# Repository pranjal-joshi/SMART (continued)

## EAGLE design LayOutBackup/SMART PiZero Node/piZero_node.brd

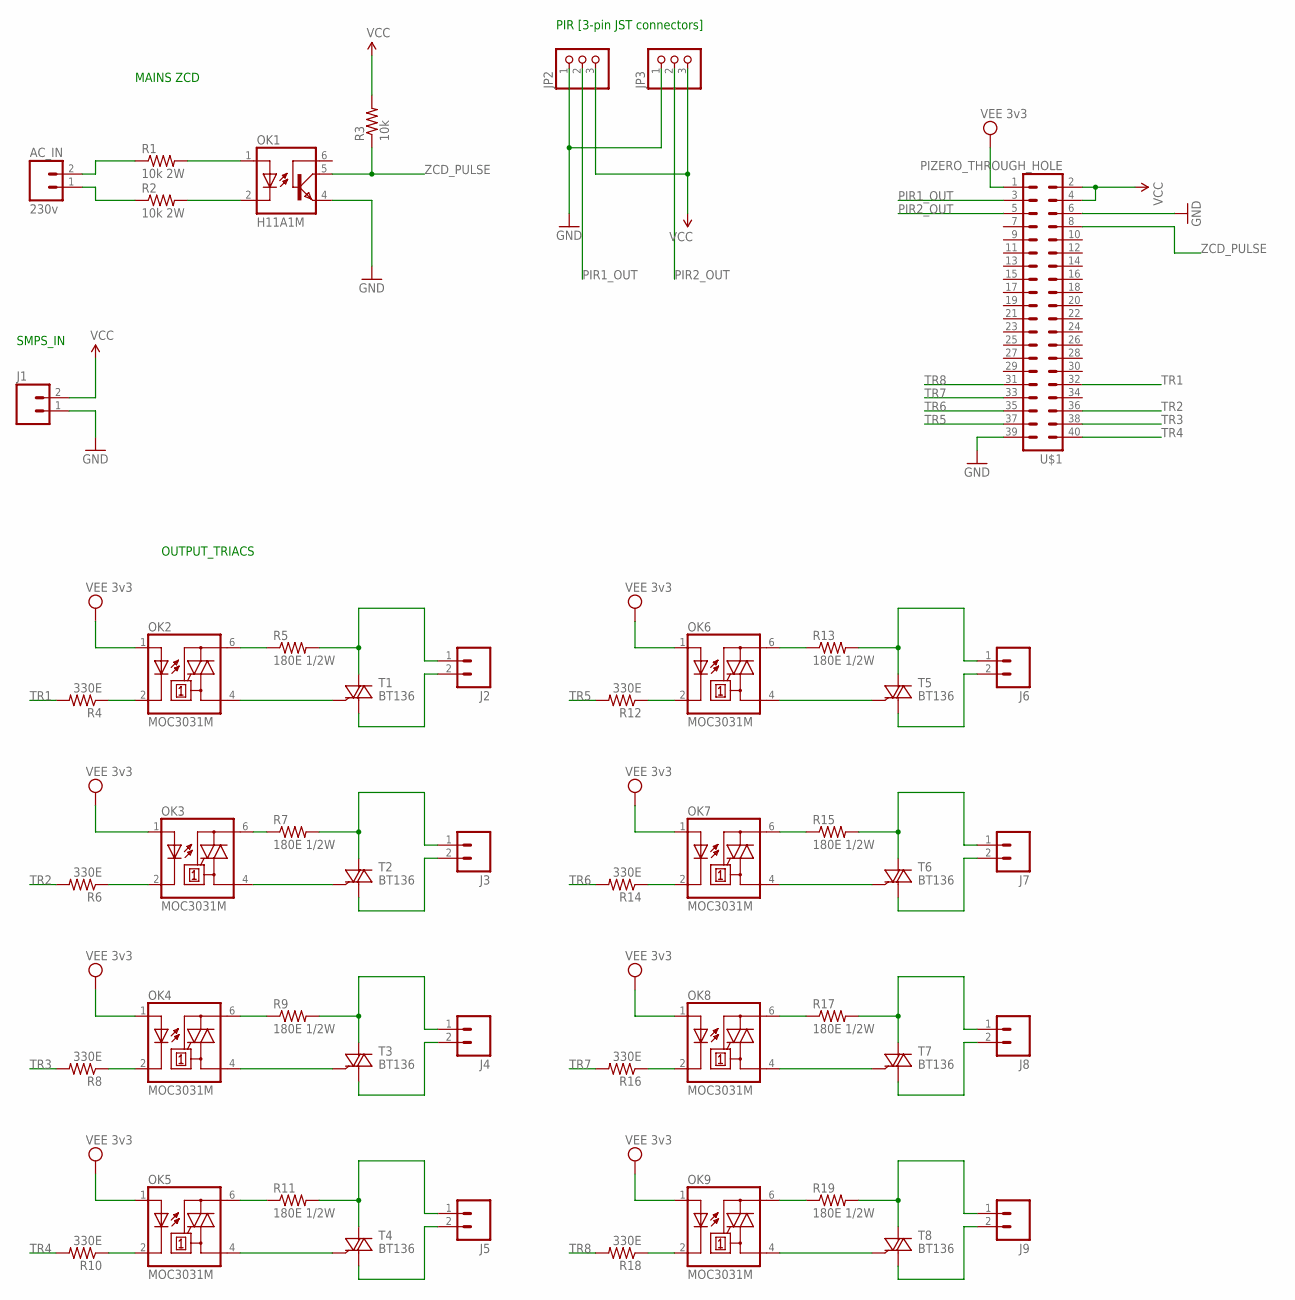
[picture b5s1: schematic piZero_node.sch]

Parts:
AC_IN: 230v; SCREWTERMINAL-3.5MM-2_LOCK
J1, J2, J3, J4, J5, J6, J7, J8, J9: M023.5MM_LOCK; SCREWTERMINAL-3.5MM-2_LOCK
JP2, JP3: PINHD-1X3; 1X03
OK1: H11A1M; DIL06
OK2, OK3, OK4, OK5, OK6, OK7, OK8, OK9: MOC3031M; DIL06
R1, R2: 10k 2W; AXIAL-0.8
R3: 10k; AXIAL-0.4
R4, R6, R8, R10, R12, R14, R16, R18: 330E; AXIAL-0.4
R5, R7, R9, R11, R13, R15, R17, R19: 180E 1/2W; AXIAL-0.5
T1, T2, T3, T4, T5, T6, T7, T8: BT136; TO220AB
U$1: PIZERO_THROUGH_HOLE; PIZERO_THOUGH_HOLE

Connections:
GND: J1.1, JP2.1, JP3.1, OK1.4 (EMI), U$1.6, U$1.39
unnamed: AC_IN.2, R1.P$1 (1)
unnamed: AC_IN.1, R2.P$1 (1)
unnamed: OK1.1 (A), R1.P$2 (2)
unnamed: OK1.2 (C), R2.P$2 (2)
unnamed: OK3.6 (A2), R7.P$1 (1)
unnamed: OK2.6 (A2), R5.P$1 (1)
unnamed: J2.1, R5.P$2 (2), T1.2 (A2)
unnamed: OK2.4 (A1), T1.3 (G)
unnamed: J2.2, T1.1 (A1)
unnamed: OK2.2 (C), R4.P$1 (1)
unnamed: J3.1, R7.P$2 (2), T2.2 (A2)
unnamed: OK3.4 (A1), T2.3 (G)
unnamed: J3.2, T2.1 (A1)
unnamed: OK3.2 (C), R6.P$1 (1)
unnamed: OK4.6 (A2), R9.P$1 (1)
unnamed: J4.1, R9.P$2 (2), T3.2 (A2)
unnamed: OK4.4 (A1), T3.3 (G)
unnamed: J4.2, T3.1 (A1)
unnamed: OK4.2 (C), R8.P$1 (1)
unnamed: OK5.6 (A2), R11.P$1 (1)
unnamed: J5.1, R11.P$2 (2), T4.2 (A2)
unnamed: OK5.4 (A1), T4.3 (G)
unnamed: J5.2, T4.1 (A1)
unnamed: OK5.2 (C), R10.P$1 (1)
unnamed: OK6.6 (A2), R13.P$1 (1)
unnamed: J6.1, R13.P$2 (2), T5.2 (A2)
unnamed: OK6.4 (A1), T5.3 (G)
unnamed: J6.2, T5.1 (A1)
unnamed: OK6.2 (C), R12.P$1 (1)
unnamed: OK7.6 (A2), R15.P$1 (1)
unnamed: J7.1, R15.P$2 (2), T6.2 (A2)
unnamed: OK7.4 (A1), T6.3 (G)
unnamed: J7.2, T6.1 (A1)
unnamed: OK7.2 (C), R14.P$1 (1)
unnamed: OK8.6 (A2), R17.P$1 (1)
unnamed: J8.1, R17.P$2 (2), T7.2 (A2)
unnamed: OK8.4 (A1), T7.3 (G)
unnamed: J8.2, T7.1 (A1)
unnamed: OK8.2 (C), R16.P$1 (1)
unnamed: OK9.6 (A2), R19.P$1 (1)
unnamed: J9.1, R19.P$2 (2), T8.2 (A2)
unnamed: OK9.4 (A1), T8.3 (G)
unnamed: J9.2, T8.1 (A1)
unnamed: OK9.2 (C), R18.P$1 (1)
PIR1_OUT: JP2.2, U$1.3
PIR2_OUT: JP3.2, U$1.5
TR1: R4.P$2 (2), U$1.32
TR2: R6.P$2 (2), U$1.36
TR3: R8.P$2 (2), U$1.38
TR4: R10.P$2 (2), U$1.40
TR5: R12.P$2 (2), U$1.37
TR6: R14.P$2 (2), U$1.35
TR7: R16.P$2 (2), U$1.33
TR8: R18.P$2 (2), U$1.31
VCC: J1.2, JP2.3, JP3.3, R3.P$2 (2), U$1.2, U$1.4
VEE: OK2.1 (A), OK3.1 (A), OK4.1 (A), OK5.1 (A), OK6.1 (A), OK7.1 (A), OK8.1 (A), OK9.1 (A), U$1.1
ZCD_PULSE: OK1.5 (COL), R3.P$1 (1), U$1.8

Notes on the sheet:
MAINS ZCD
SMPS_IN
PIR [3-pin JST connectors]
OUTPUT_TRIACS

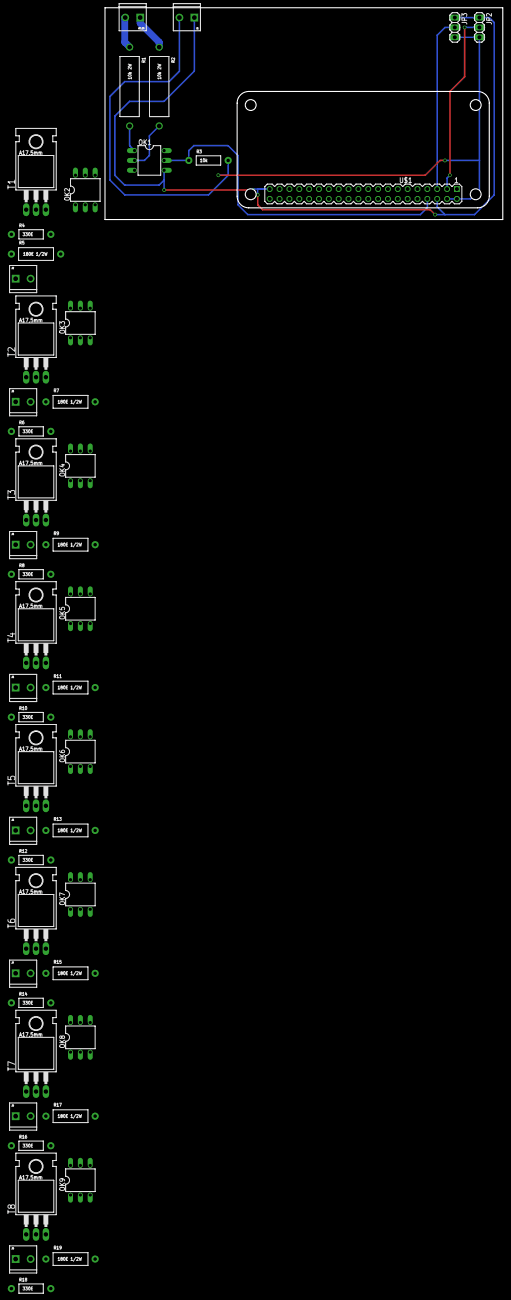
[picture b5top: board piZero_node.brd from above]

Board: 2 copper layers, 102.5 x 54.6 mm, 49 parts (0 on the bottom side), 58 nets.

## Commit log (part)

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2020-06-14 sub to gateway if net is available
2020-06-14 TODO: implement routing in decisionMaker
2020-06-14 broadcastStateChanged added
2020-06-14 getState bug fixed and optimized
2020-06-14 bugfixes
2020-06-14 Gateway routing impeoved TODO - dbg mesh.stop
2020-06-16 ntp added while mqtt connection
2020-06-16 NTP broadcast packet added
2020-06-16 ntpStruct added
2020-06-16 NTP functions added
2020-06-17 TODO - Impliment timer packet
2020-06-18 timeStruct added
2020-06-18 TODO - implement jsonTimerParser
2020-06-18 timerStructure updated
2020-06-18 save and load timer implemented
2020-06-18 parsers added to decisionMaker
2020-06-18 parseTimer and parseNTP implemented
2020-06-18 optimized
2020-06-18 debug mesh connection - instability
2020-06-19 minor improvements
2020-06-20 Major bugfix - Mesh disconnect on ntp.begin()
2020-06-20 scan MESH if TARGET unavailable to acquire channel
    Also stop searchTargetTask if anyone is ROOT because its online
2020-06-21 mesh ssid & pass added
2020-06-21 Mesh SSID, PASS & channel JS added
2020-06-21 todo - fix target ssid not found bug
2020-06-21 soft_reset added
2020-06-21 personalize MESH network while CONF
    JSON_BUF_SIZE > 768 will cause a PANIC dump in stateChangedBroadcast
2020-06-21 get set Raw methods added
2020-06-21 struct updated
2020-06-21 todo - Debug fsys.loadTimers dump
2020-06-21 timerSchedHandlerTask added
2020-06-21 Check & implement TODOs
2020-06-22 timerStruct now have ignore time of 60 sec
2020-06-22 loadTimers PANIC resolved, not using fsys.loadTimers now
2020-06-23 preprocessors added for SWITCHING & SENSOR
2020-06-23 constants replaced with #define
2020-06-23 SensorLink JSON parser added
2020-06-23 Sensor Functions added
2020-06-23 Check todos!
2020-06-24 get set by sensor methods added
2020-06-25 get set by Timer added
2020-06-25 New methods added and bugfixes
2020-06-25 Sensor broadcast parser implemented
2020-06-25 Light & DHT removed
2020-06-25 todo - implement mesh sensor to MQTT routing
2020-06-26 mesh json print on connection callback
2020-06-26 Fingerprints added
2020-06-30 topic added to sensor_broadcast
2020-06-30 sensor_broadcast publish routing added
2020-06-30 Flutter project created
2020-06-30 OTA save/load added
2020-06-30 OTA methods added
2020-06-30 OTA update handler implemented
2020-06-30 OTA packet panic core fixed
2020-07-03 SENSOR PIN - FUNCTION_3
2020-07-03 Pin switching between Serial & GPIO for ESP-01
2020-07-03 config updated for NOD=2, NOD=1
2020-07-03 IO class updated for NOD=2, NOD=1
2020-07-03 initiali update NOD=2, NOD=1 implemented
2020-07-03 WIll Message implemented
2020-07-03 Routing of STATUS packet from Gateway -> MQTT
2020-07-03 Vector_Link added for reflecting STATUS from Mesh -> MQTT
    Review To-Dos
2020-07-05 ID implemented for AsyncOTA
2020-07-05 Vector Link implemented to send STATTUS to MQTT
2020-07-05 JSON fixes
2020-07-05 stateVar inverted for ACTIVE LOW in NoD < 4
2020-07-05 Sensor improvements
2020-07-05 ToDo: Sensor GPIO selection & testing
2020-07-06 PIN config changed for Sensor
2020-07-06 Replaced ElegantOTA with ESP8266HTTPUpdater
    #define WEBSERVER_H removes redeclaration error
2020-07-06 getNodeInfo now shows VERSION
2020-07-06 curl command added in comment
2020-07-12 NoD 2 Pin config changed
2020-07-12 NOD 2 PCB routing completed
2020-07-17 PDF sch added
2020-07-18 Protocol Changed
2020-07-19 Flutter development started
2020-07-20 MQTT IP changed
2020-07-20 Profile Cards updation in progress
2020-07-20 Cards Added and improved
2020-07-21 ThemeData - WIP
2020-07-22 Dotted border added
2020-07-22 SwitchboardTile and Class added
2020-07-22 TabViewBar implemented
2020-07-22 Improvements and fixes
2020-07-22 State management implemented
2020-07-22 Size and UI improvements
2020-07-22 UI Improvements
2020-07-22 Debug and fix only one expansion at a time
2020-07-23 Improvements & fixes
2020-07-24 JSON models class created
2020-07-24 MQTT Client implemented
2020-07-24 Minor updates
2020-07-24 MQTT handlers and switch logic added
2020-07-24 Fix MQTT class with same connection but multiple callbacks
2020-07-26 Model classes updated
2020-07-26 BroadcastStream implemented with singleton class
2020-07-26 WIP - Switch auto toggle as per State Progress
2020-07-26 Fetching added - room name, NoD, smartId - Dynamic SwitchboardRow implemented
2020-07-26 Fixes and Improvements
2020-07-27 Error Handling and cleanup methods added
2020-07-27 IconData serialization with iconCode added
2020-07-27 ValueKey implemented
2020-07-27 UI error fixes + MQTT SwitchRow WIP
2020-07-27 NoD error handling added
2020-07-28 topic type added
2020-07-28 WIP - publish SwitchboardRow list
2020-07-28 Appbar UI updated - iOS friendly
2020-07-28 SVG files added
2020-07-28 AppBar update
2020-07-29 SSID updated to 17 chars
    SMART_12345678_NoD/Flag char at last
2020-07-29 Topic enum implemented
2020-07-29 SVGs added
2020-07-29 configureDevice page created
2020-07-29 Add New Device - completed
2020-07-31 wifi connection added on tap
2020-07-31 WIP - Debug HttpException
2020-07-31 Debug HttpException
2020-08-02 App Compatibility - Now respond with Json of scanned wifi instead of HTML
2020-08-02 Moved!
2020-08-03 Improvement - Mesh nodes now Search for target SSID when Root node drops
2020-08-03 Configuration Process completed! TODO: Sync SP with MQTT
2020-08-03 TODO: Implement MQTT sync buffer that for syncing onConnect
2020-08-03 MqttBuffer implemented for offline save and sync
2020-08-03 Implement TODOs
2020-08-03 static 'type' for App to App msgs via MQTT
2020-08-04 Sync class created
2020-08-04 Test SyncClass
2020-08-04 Location dropdown added
2020-08-04 Bad Stream: Error Handling added
2020-08-04 Add new room - Implemented, check TODOs
2020-08-06 ToDo - Improve iconData serialization
2020-08-06 Flutter SDK 1.20 Upgrade
2020-08-06 Crash fixes
2020-08-06 Box icons issue fixed
2020-08-06 WIP - Check TODOs
2020-08-07 TextFormField widget seprated
2020-08-07 saveToDisk and loadFromDisk methods added
    Implemented static mehtods to handle IO with shared prefs
2020-08-07 loadFromDiskAsString method added
2020-08-08 loadFromDisk and SaveToDisk methods added
2020-08-08 Buffers added to publishBuffer to publish whole lists
2020-08-08 Not auto-disconnect on connect failure
2020-08-08 WIP - Fix TODOs
2020-08-09 Dynamic add new room + validation snackbars added
2020-08-09 Class names changed for 'Pages'
2020-08-09 Fixes & Improvements
2020-08-09 WIP - LoginPage created
2020-08-09 Overflow fixed & UI improvised
2020-08-09 Checkbox widget added
2020-08-10 WiFi dropdown to FutureBuilder
2020-08-10 Dropdown widget added
2020-08-10 WIP - Check widgets in TODO
2020-08-10 Minor changes for Testing
2020-08-10 Dropdown state bug fix
    WIP - New bug introduced! Can't connect to the smart's network
2020-08-11 Minor Improvements & fixes
2020-08-11 Signup page added
2020-08-11 Firebase conffigured
2020-08-11 WIP - Test Firebase signup!
2020-08-11 gradle build system errors fixed
2020-08-11 Improvised - Focus to next
2020-08-11 Render Fix - Red wifilist in future builder
2020-08-11 Layout improvements
2020-08-11 Signup completed - Both UI & Firebase
2020-08-14 src files renamed
2020-08-14 New methods added for credential mgmt
2020-08-14 Login page implemented, tested & fixes
2020-08-14 Progress Spinner added
2020-08-14 Glowin Indicator Widget for Room Status
2020-08-14 WIP - Home page in progress
2020-08-14 WIP todos
2020-08-15 Password Recovery & Verification added
2020-08-15 Forgot Password Implemented
2020-08-15 state packet now contains nodename
2020-08-15 nodename added to Node -> App state packet
2020-08-15 go back on snackbar closing callback
2020-08-15 null saftey on enum
2020-08-15 Network check added
2020-08-15 subscribe to state methods added with SmartID
2020-08-15 PowerIndicator implemented for RoomCards in gridview
2020-08-16 WelcomeCard for homepage added
2020-08-16 JsonNodeStatus with provided
2020-08-16 Welcome Banner & card added
2020-08-17 Minor Fixes & improvements
2020-08-17 NodeStatusProvider created
2020-08-17 StatusBarColor removed & improvised
2020-08-17 Minor Changes
2020-08-17 WIP - Create a Room page
2020-08-17 UI enhanced
2020-08-17 JsonNodeState provider implemented
2020-08-18 Custom Exception implemented
2020-08-18 Code Duplication Removed
2020-08-18 Logical Classes are noew Heavily Documented!
2020-08-19 Helper Class moved & renamed
2020-08-19 SyncWithProvider method added
2020-08-20 Custom Card Widget with Subtle Shadow
2020-08-20 Native Cards replaced with Custom Cards for beautiful shadow
2020-08-20 Multi-level stack added to UI
2020-08-20 SmartCard wrapper added
2020-08-20 Stack UI improved! Setup widget added
2020-08-21 Minor Fixes
2020-08-22 WIP - Profile cards Horizontal Scroll implemented
2020-08-24 DeviceCard UI Implemented
2020-08-25 Label Provider added for managing device names
2020-08-25 Optimized for LabelProvider
2020-08-25 getStateBySmartId method added
2020-08-25 Providers Optimized
2020-08-25 SmartExceptions added to SmartMqtt
2020-08-25 SmartDeviceData Model Updated
2020-08-25 Separate PubSub topics
2020-08-25 Room Reset Confirm Alert Dialog added
2020-08-26 Exceptions improvised
2020-08-26 New getter method added
2020-08-26 ConnectivityProvider implemented
2020-08-26 publish states to gateway on switch toggle added
2020-08-26 No Internet Alert Dialog added with Connectivity Provider
2020-08-28 trim() added
2020-08-28 Shadow animation added
2020-08-28 Device Page Created
2020-08-28 No Network Alert Fixed
2020-08-29 LineAwesome package replaced
2020-08-29 DarkIconTheme added
2020-08-29 toggleNodeSwitchState method added
2020-08-29 control list implemented
2020-08-30 time picker theme added
2020-08-30 popup menu icon color fix
2020-08-30 version update
2020-08-30 TimePicker and WeekDaySelector Implemented
2020-09-04 Minor Gradle changes
2020-09-05 save button UI rounded corners removed
2024-05-03 TImeout reduced, led blink added
2024-05-11 webserver class aded and creds updated
2024-05-11 webserver added to obtain config
2024-05-11 File system implemented with eSPIFFS and Config webpage updated
2024-05-12 WIP - HTTP GET Handle & Save/Load config
2024-05-12 Working - HTTP Get with Config Save/Load
2024-05-12 UI updated to modern
2024-05-12 GUI updated to mordern, HttpUpdater & WebServer enhanced - WIP factory reset and Re-scan
2024-05-13 Create configure.html
    Provisioning page finalized - %% escaped for AsyncWebServer processor
2024-05-13 pages added
2024-05-13 Working prototype
2024-05-13 Create dummy
2024-05-13 Flux PCB files added
2024-05-13 Minor enhancements
2024-05-14 Arduino folder structure updated
2024-05-14 Defaulted to nodemcu
2024-05-14 Brand logo added to config page as base64
2024-05-14 Minor UI fixes
2024-05-14 Alexa listener added with devices
2024-05-15 off_timeout bugfixed, sensor state WIP for alexa control
2024-05-15 Toggle switch added in UI and Alexa braodcast stateChange to control motion sensor
2024-05-16 String comparision bugfix in GET /state
2024-05-18 OneButton based button added for reset, enable & disable
2024-05-18 Bugfix for no networks shown in AP mode
2024-05-19 WIP - ezLED added for visual feedback
2024-05-20 Removed WiFi multi to eliminate blocking delays in loop that affects AP serving and other LED/button operations
2024-05-20 Bugfixes and Perf upgrades
2024-05-20 Debug statements fixed
2024-05-20 button & led setup moved at begining, WiFi wait added before starting server
2024-05-27 LED & preprocessor changed
2024-05-28 Separate config for ESP01-S
2024-05-28 WIP - Pin update for ESP01-S
2024-05-29 SERIAL_TX_ONLY added in begin for ESP01/ESP01-S
2024-05-30 led working for ESP01/S & NodeMCU
2024-05-30 HTTPS validation added for URL box
2024-05-30 Moved to ElegantOTA v3
2024-05-30 Github pages link added
2024-05-30 GH pages link added
2024-05-30 PCB layout added
2024-05-31 VERSION added for nodemcu
2024-05-31 Moved back to AsyncElegantOTA
2024-06-01 NODEMCU Led changed to GPIO16
2024-06-02 Minified removed as JS fails in minified
2024-06-03 timer_ignore_sensoe added to reduce false positives
2024-06-23 Loop delay reduced, config set to nodemcu
2025-04-22 RSSI, Internal Temp and Uptime added
2025-05-12 g0 to g8 enabled
2025-05-20 Added motion control blueprint
2025-06-06 Blueprint for updating scene when device state changes manually
2025-06-26 Added BT proxy
